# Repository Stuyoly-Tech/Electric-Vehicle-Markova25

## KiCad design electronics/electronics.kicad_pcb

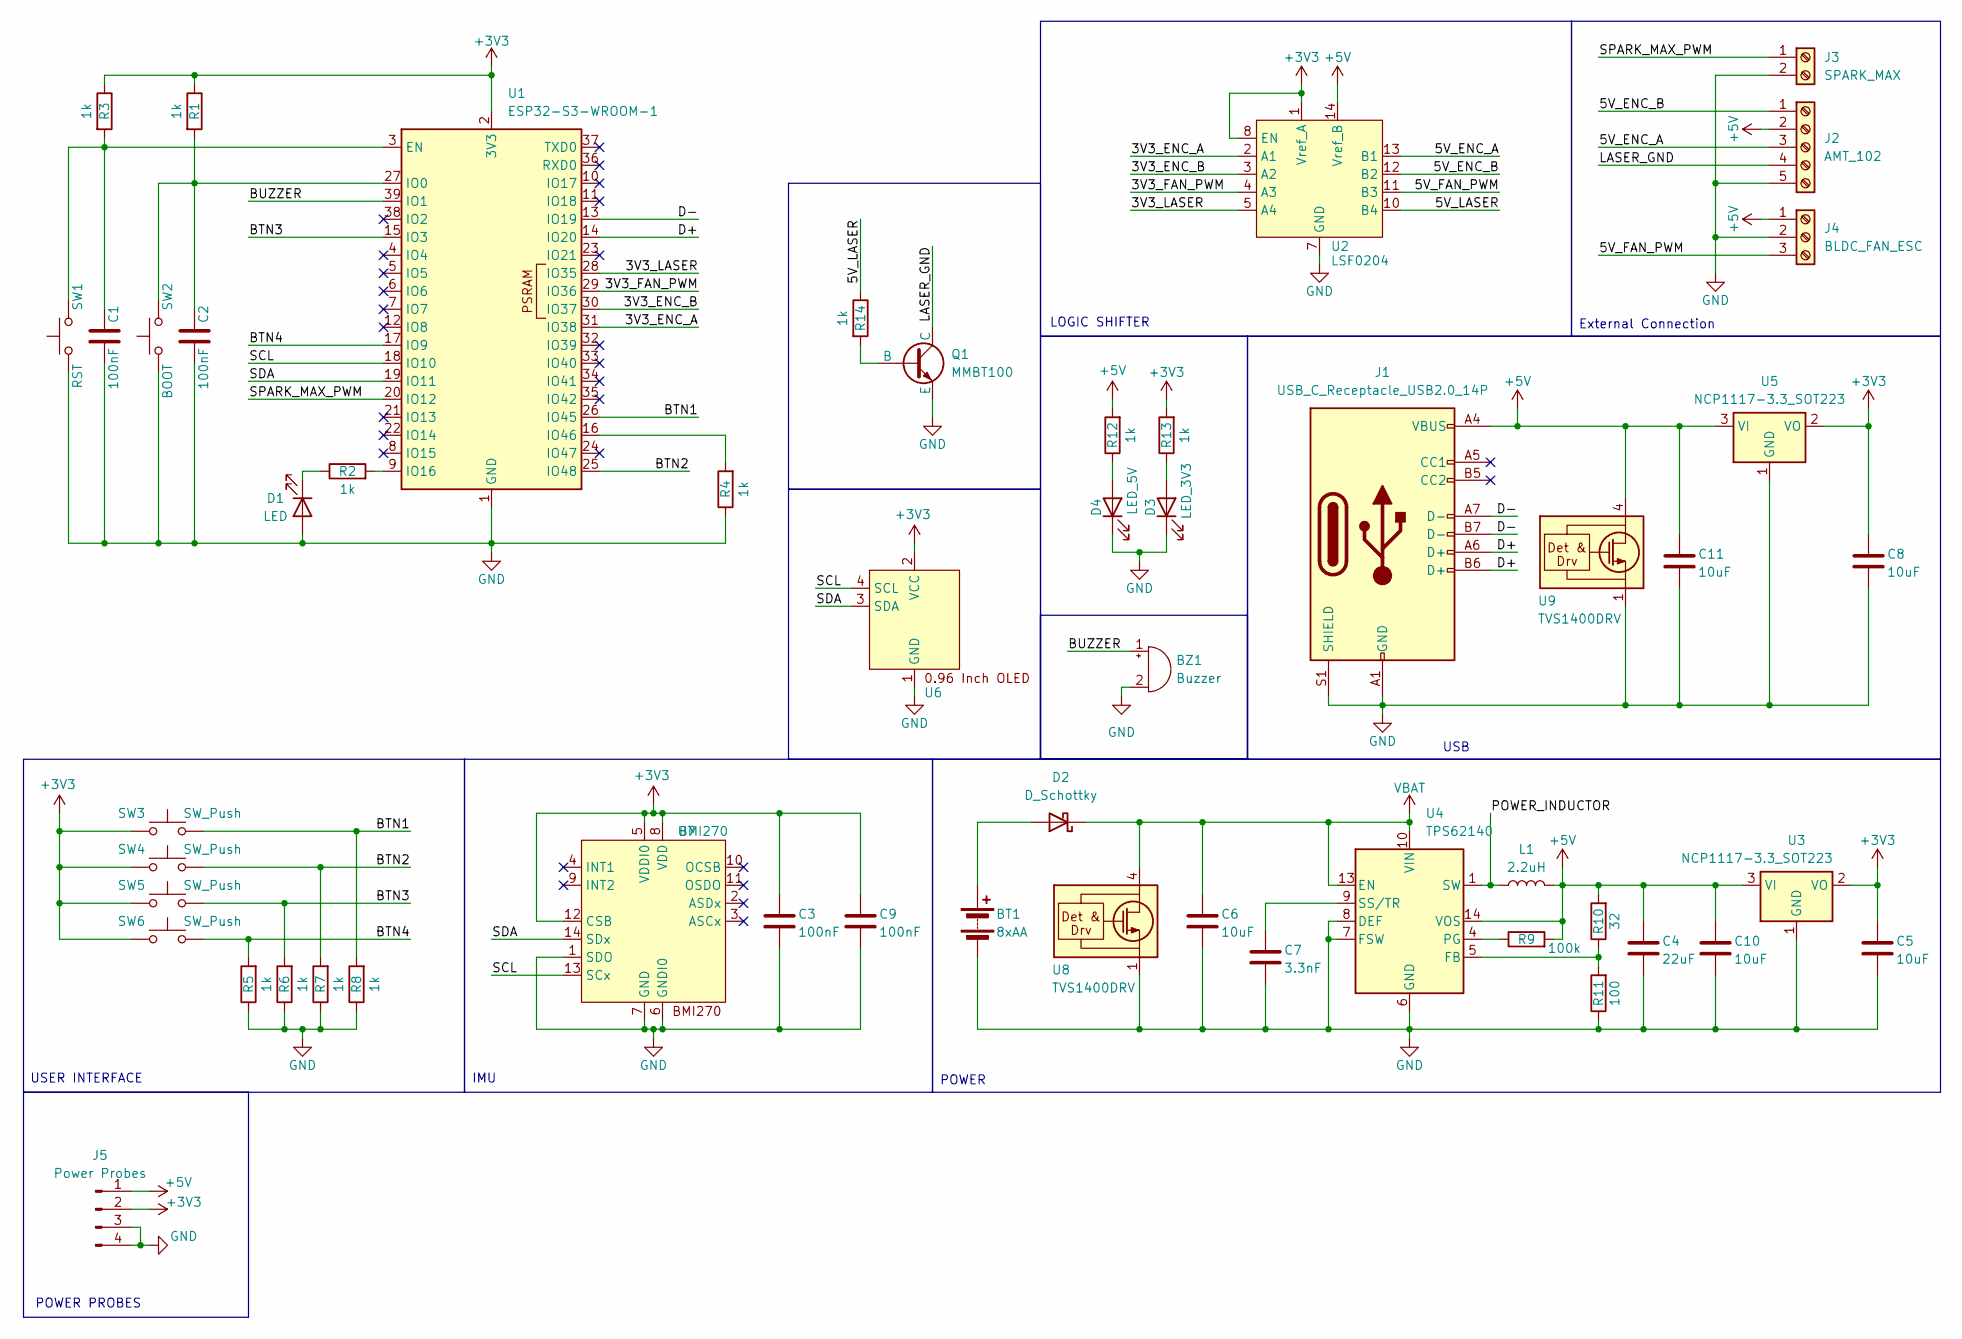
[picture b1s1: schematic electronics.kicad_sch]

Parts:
BT1: 8xAA; TerminalBlock_Phoenix_PT-1,5-2-5.0-H_1x02_P5.00mm_Horizontal
BZ1: Buzzer; Buzzer_12x9.5RM7.6
C1, C2, C3, C9: 100nF; C_0603_1608Metric
C4: 22uF; C_0805_2012Metric
C5, C6, C8, C10, C11: 10uF; C_0805_2012Metric
C7: 3.3nF; C_0603_1608Metric
D1: LED; LED_0603_1608Metric
D2: D_Schottky; TO-277A
D3: LED_3V3; LED_0603_1608Metric
D4: LED_5V; LED_0603_1608Metric
J1: USB_C_Receptacle_USB2.0_14P; USB_C_Receptacle_GCT_USB4110
J2: AMT_102; TerminalBlock_Phoenix_PT-1,5-5-5.0-H_1x05_P5.00mm_Horizontal
J3: SPARK_MAX; TerminalBlock_Phoenix_PT-1,5-2-5.0-H_1x02_P5.00mm_Horizontal
J4: BLDC_FAN_ESC; TerminalBlock_Phoenix_PT-1,5-3-5.0-H_1x03_P5.00mm_Horizontal
J5: Power Probes; PinHeader_1x04_P2.54mm_Vertical
L1: 2.2uH; L_Vishay_IHLP-1212
Q1: MMBT100; SOT-23-3
R1, R2, R3, R4, R5, R6, R7, R8, R12, R13, R14: 1k; R_0603_1608Metric
R9: 100k; R_0603_1608Metric
R10: 32; R_0603_1608Metric
R11: 100; R_0603_1608Metric
SW1: RST; SW_SPST_EVQP2
SW2: BOOT; SW_SPST_EVQP2
SW3, SW4, SW5, SW6: SW_Push; SW_Push_1P1T_NO_6x6mm_H9.5mm
U1: ESP32-S3-WROOM-1
U2: LSF0204; Texas_S-PVQFN-N14
U3, U5: NCP1117-3.3_SOT223; SOT-223-3_TabPin2
U4: TPS62140; VQFN-16-1EP_3x3mm_P0.5mm_EP1.68x1.68mm_ThermalVias
U6: PinHeader_1x04_P2.54mm_Vertical
U7: BMI270; Bosch_LGA-14_3x2.5mm_P0.5mm
U8, U9: TVS1400DRV; WSON-6-1EP_2x2mm_P0.65mm_EP1x1.6mm_ThermalVias

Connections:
+3V3: C3.1, C5.1, C8.1, C9.1, J5.2, R1.1, R3.1, R13.2, SW3.1, SW4.1, SW5.1, SW6.1, U1.2 (3V3), U2.1 (Vref_A), U2.8 (EN), U3.2 (VO), U5.2 (VO), U6.2 (VCC), U7.5 (VDDI0), U7.8 (VDD), U7.12 (CSB)
+5V: C4.1, C10.1, C11.1, J1.A4 (VBUS), J1.A9 (VBUS), J1.B4 (VBUS), J1.B9 (VBUS), J2.2, J4.1, J5.1, L1.2, R9.2, R10.2, R12.2, U2.14 (Vref_B), U3.3 (VI), U4.14 (VOS), U5.3 (VI), U9.4 (IN), U9.5 (IN), U9.6 (IN)
/3V3_ENC_A: U1.31 (IO38), U2.2 (A1)
/3V3_ENC_B: U1.30 (IO37), U2.3 (A2)
/3V3_FAN_PWM: U1.29 (IO36), U2.4 (A3)
/3V3_LASER: U1.28 (IO35), U2.5 (A4)
/5V_ENC_A: J2.3, U2.13 (B1)
/5V_ENC_B: J2.1, U2.12 (B2)
/5V_FAN_PWM: J4.3, U2.11 (B3)
/5V_LASER: R14.1, U2.10 (B4)
/BTN1: R8.2, SW3.2, U1.26 (IO45)
/BTN2: R7.2, SW4.2, U1.25 (IO48)
/BTN3: R6.2, SW5.2, U1.15 (IO3)
/BTN4: R5.2, SW6.2, U1.17 (IO9)
/BUZZER: BZ1.1 (+), U1.39 (IO1)
/D+: J1.A6 (D+), J1.B6 (D+), U1.14 (IO20)
/D-: J1.A7 (D-), J1.B7 (D-), U1.13 (IO19)
/LASER_GND: J2.4, Q1.1 (C)
/POWER_INDUCTOR: L1.1, U4.1 (SW), U4.2 (SW), U4.3 (SW)
/SCL: U1.18 (IO10), U6.4 (SCL), U7.13 (SCx)
/SDA: U1.19 (IO11), U6.3 (SDA), U7.14 (SDx)
/SPARK_MAX_PWM: J3.1, U1.20 (IO12)
GND: BT1.2 (-), BZ1.2 (-), C1.2, C2.2, C3.2, C4.2, C5.2, C6.2, C7.2, C8.2, C9.2, C10.2, C11.2, D1.2 (A), D3.1 (K), D4.1 (K), J1.A1 (GND), J1.A12 (GND), J1.B1 (GND), J1.B12 (GND), J1.S1 (SHIELD), J2.5, J3.2, J4.2, J5.3, J5.4, Q1.3 (E), R4.1, R5.1, R6.1, R7.1, R8.1, R11.1, SW1.1, SW2.1, U1.1 (GND), U1.40 (GND), U1.41 (GND), U2.7 (GND), U3.1 (GND), U4.6 (GND), U4.7 (FSW), U4.8 (DEF), U4.15 (GND), U4.16 (GND), U4.17 (GND), U5.1 (GND), U6.1 (GND), U7.1 (SDO), U7.6 (GNDI0), U7.7 (GND), U8.1 (GND), U8.2 (GND), U8.3 (GND), U8.7 (GND), U9.1 (GND), U9.2 (GND), U9.3 (GND), U9.7 (GND)
unnamed: BT1.1 (+), D2.2 (A)
unnamed: D1.1 (K), R2.1
unnamed: D3.2 (A), R13.1
unnamed: D4.2 (A), R12.1
unnamed: Q1.2 (B), R14.2
unnamed: C1.1, R3.2, SW1.2, U1.3 (EN)
unnamed: C2.1, R1.2, SW2.2, U1.27 (IO0)
unnamed: R2.2, U1.9 (IO16)
unnamed: R4.2, U1.16 (IO46)
unnamed: R10.1, R11.2, U4.5 (FB)
unnamed: R9.1, U4.4 (PG)
unnamed: C7.1, U4.9 (SS/TR)
VBAT: C6.1, D2.1 (K), U4.10 (VIN), U4.11 (VIN), U4.12 (VIN), U4.13 (EN), U8.4 (IN), U8.5 (IN), U8.6 (IN)

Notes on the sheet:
USER INTERFACE
POWER PROBES
POWER
IMU
LOGIC SHIFTER
USB
External Connection

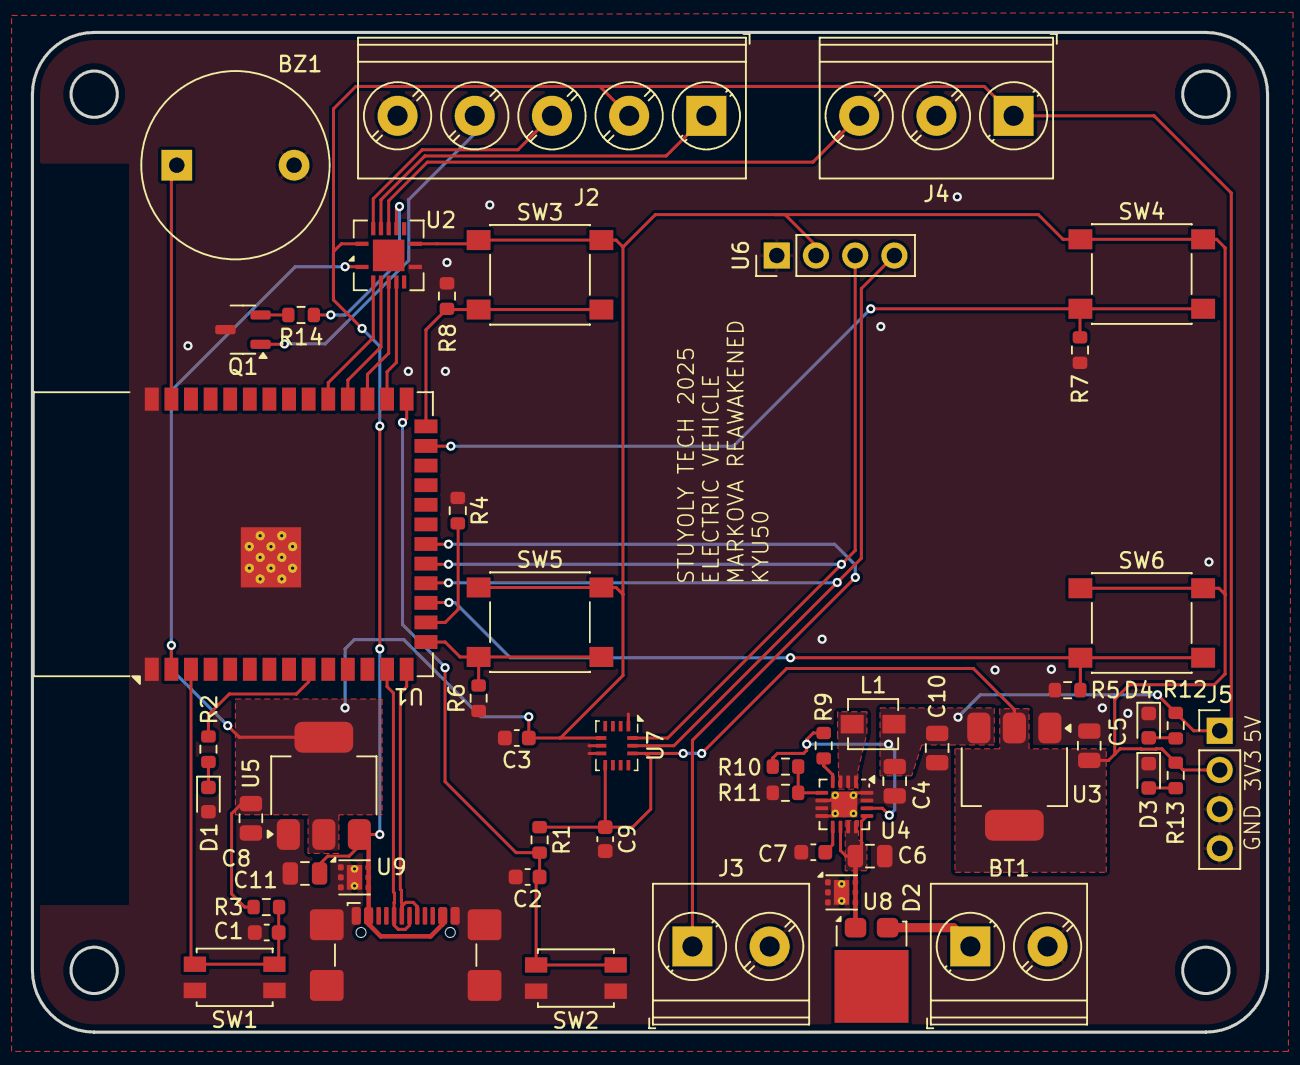
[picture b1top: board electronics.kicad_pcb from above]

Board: 2 copper layers, 80.0 x 64.8 mm, 53 parts (0 on the bottom side), 36 nets.

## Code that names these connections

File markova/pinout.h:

#ifndef PINOUT_H
#define PINOUT_H

//I2C
#define SDA 10
#define SCL 11

//Motors
#define SPARK_MAX_PWM 12
#define FAN_PWM 36

//Laser
#define LASER 36

//Buzzer
#define BUZZER 1

//LED
#define STATUS_LED 16

//Encoder
#define ENC_A 38
#define ENC_B 37


//Interface
#define BTN0 45
#define BTN1 48
#define BTN2 9
#define BTN3 3

#endif

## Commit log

2025-03-31 basic schematic
2025-04-17 Power supply + status LEDs complete, External connections complete, Logic shifter complete
2025-04-21 needs routing to decide pin placements
2025-04-24 need to route switching psu correctly
2025-04-28 ready to ship out
2025-04-28 fix spelling
2025-04-28 added laser to pcb
2025-04-28 lgtm
2025-04-29 transistor + ready
2025-05-04 copied from mcqueen code
2025-05-04 changed file name
2025-05-04 updated pinout
2025-05-05 kellen: write the code. Checed: Yes sir. Gurt: Yo
2025-05-18 configured pinout
2025-05-18 ticks r geeked
2025-05-19 PRE PID TUNING
2025-11-18 changing for 2026 season
